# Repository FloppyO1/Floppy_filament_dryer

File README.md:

# Floppy Filament Dryer

This project is a controller board designed for a small electric oven, transforming it into a filament dryer for 3D printing. The controller allows precise temperature management, helping keep your filament dry and ready to use.

## Features

- Temperature control for effective filament drying
- Multiple materials presets
- Timer function
- Two custom material temp available
- Compatible with standard electric ovens
- Easy setup and integration

## YouTube Video

Watch it in action: [Filament Dryer Demo](https://youtu.be/55DRHrMC5Mg)

## License

This project is open source. See the LICENSE file for more details.

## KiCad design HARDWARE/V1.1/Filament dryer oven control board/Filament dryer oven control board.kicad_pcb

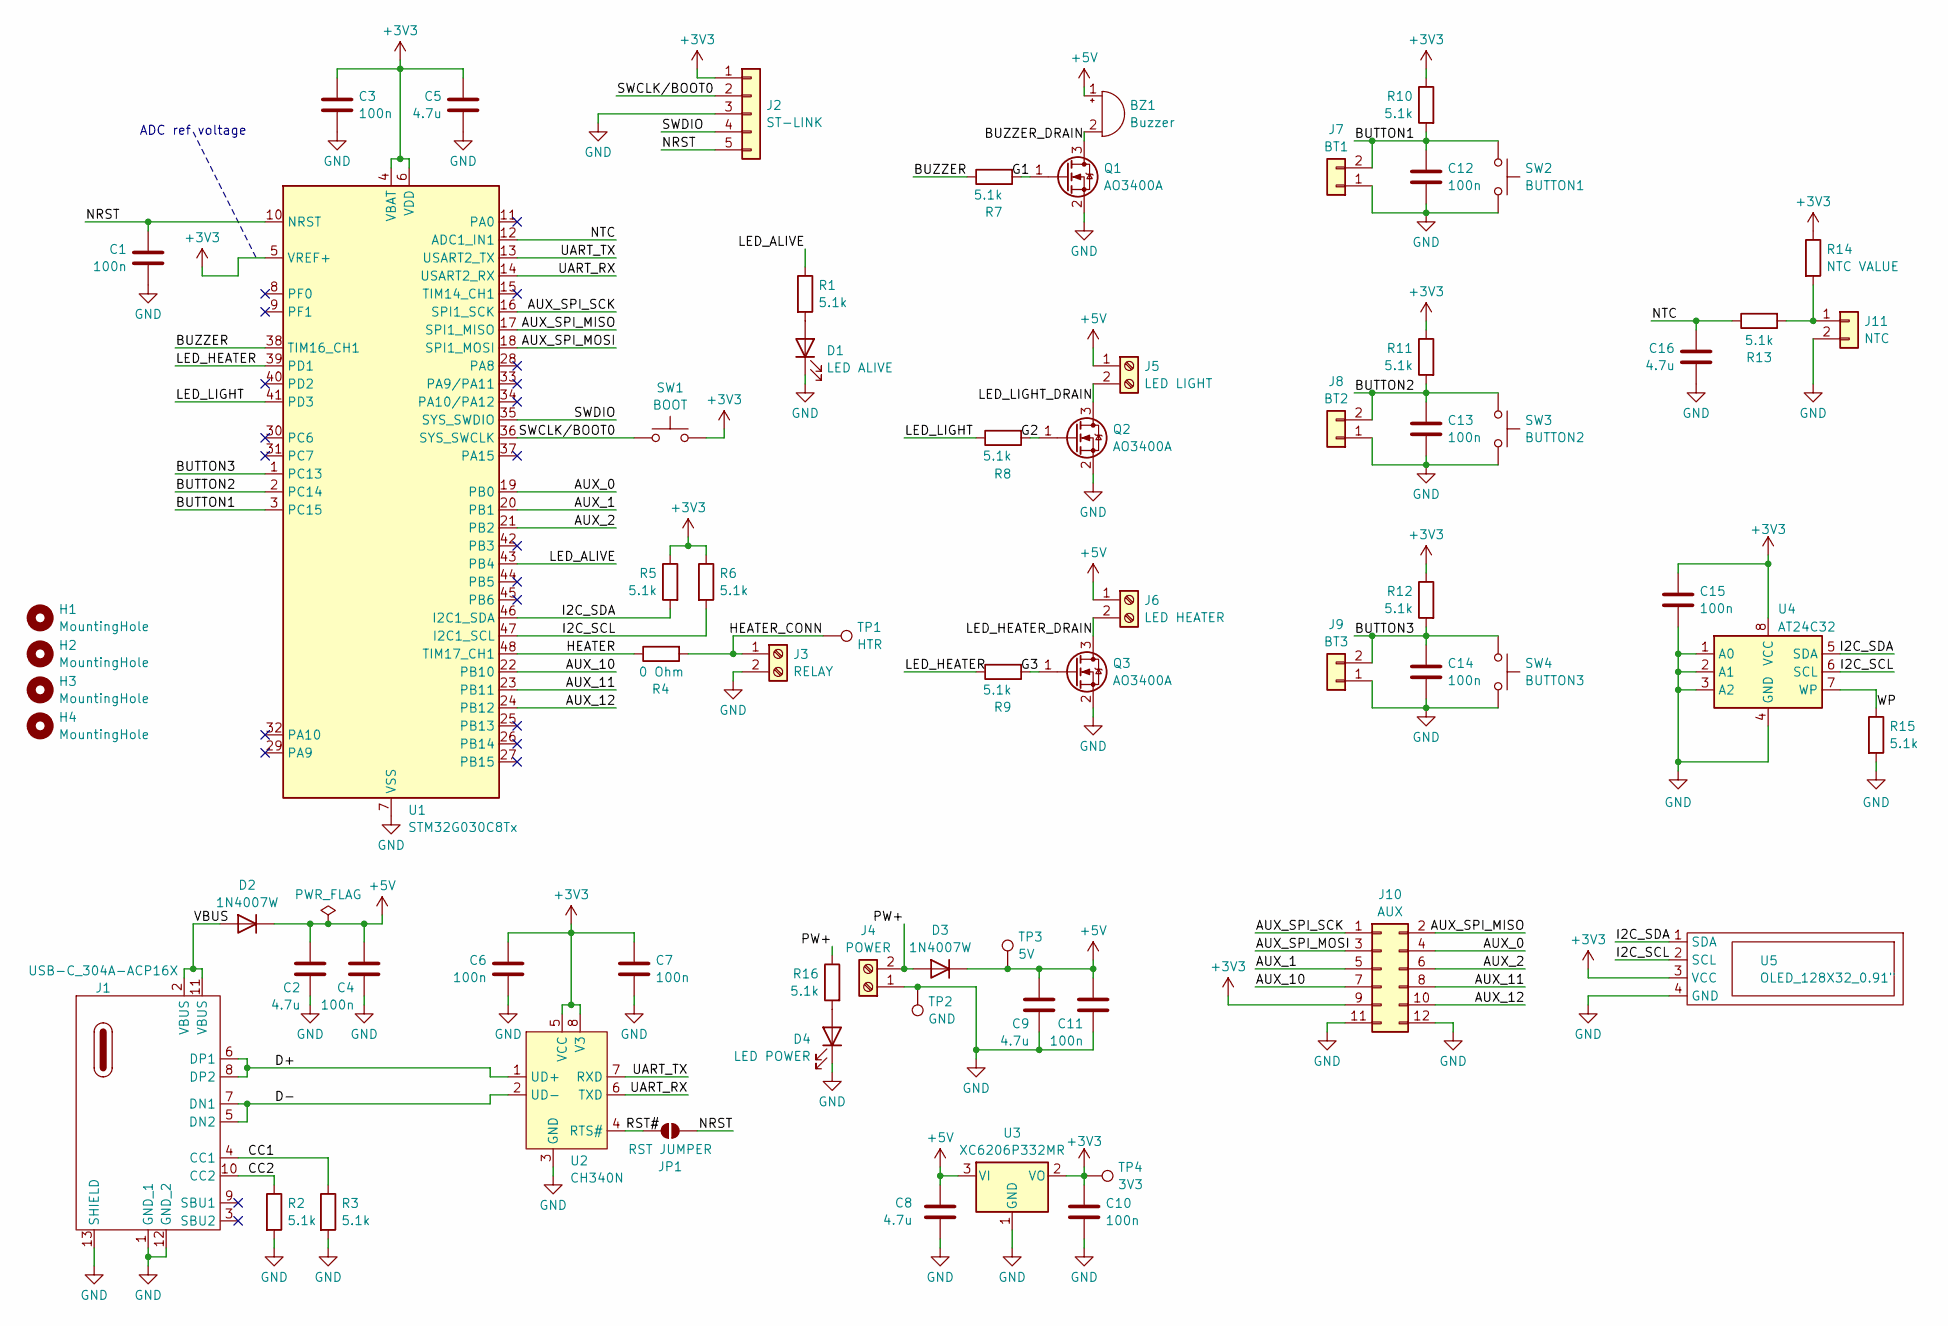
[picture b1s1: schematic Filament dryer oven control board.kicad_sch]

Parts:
BZ1: Buzzer; Buzzer_12x9.5RM7.6
C1, C3, C4, C6, C7, C10, C11, C12, C13, C14, C15: 100n; C_0805_2012Metric_Pad1.18x1.45mm_HandSolder
C2, C5, C8, C9, C16: 4.7u; C_0805_2012Metric_Pad1.18x1.45mm_HandSolder
D1: LED ALIVE; LED_0805_2012Metric_Pad1.15x1.40mm_HandSolder
D2, D3: 1N4007W; D_SOD-123F; LCSC C7528871
D4: LED POWER; LED_0805_2012Metric_Pad1.15x1.40mm_HandSolder
H1, H2, H3, H4: MountingHole; MountingHole_3.2mm_M3_Pad_Via
J1: USB-C_304A-ACP16X; USB_C_304A-ACP16X
J2: ST-LINK; PinHeader_1x05_P2.54mm_Vertical
J3: RELAY; TerminalBlock_bornier-2_P5.08mm
J4: POWER; TerminalBlock_bornier-2_P5.08mm
J5: LED LIGHT; TerminalBlock_bornier-2_P5.08mm
J6: LED HEATER; TerminalBlock_bornier-2_P5.08mm
J7: BT1; JST_XH_B2B-XH-A_1x02_P2.50mm_Vertical
J8: BT2; JST_XH_B2B-XH-A_1x02_P2.50mm_Vertical
J9: BT3; JST_XH_B2B-XH-A_1x02_P2.50mm_Vertical
J10: AUX; PinHeader_2x06_P2.54mm_Vertical
J11: NTC; JST_XH_B2B-XH-A_1x02_P2.50mm_Vertical
JP1: RST JUMPER; SolderJumper-2_P1.3mm_Open_RoundedPad1.0x1.5mm
Q1, Q2, Q3: AO3400A; SOT-23
R1, R2, R3, R5, R6, R7, R8, R9, R10, R11, R12, R13, R15, R16: 5.1k; R_0805_2012Metric_Pad1.20x1.40mm_HandSolder
R4: 0 Ohm; R_0805_2012Metric_Pad1.20x1.40mm_HandSolder
R14: NTC VALUE; R_0805_2012Metric_Pad1.20x1.40mm_HandSolder
SW1: BOOT; SW-SMD_TS24CA SMD BUTTO 90deg
SW2: BUTTON1; SW_SPST_SKQG_WithoutStem
SW3: BUTTON2; SW_SPST_SKQG_WithoutStem
SW4: BUTTON3; SW_SPST_SKQG_WithoutStem
TP1: HTR; TestPoint_THTPad_1.0x1.0mm_Drill0.5mm
TP2: GND; TestPoint_THTPad_1.0x1.0mm_Drill0.5mm
TP3: 5V; TestPoint_THTPad_1.0x1.0mm_Drill0.5mm
TP4: 3V3; TestPoint_THTPad_1.0x1.0mm_Drill0.5mm
U1: STM32G030C8Tx; LQFP-48_7x7mm_P0.5mm
U2: CH340N; SOP-8_3.9x4.9mm_P1.27mm
U3: XC6206P332MR; SOT-23-3
U4: AT24C32; SO-8_3.9x4.9mm_P1.27mm
U5: OLED_128X32_0.91"; PinSocket_1x04_P2.54mm_Vertical

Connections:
+3V3: C3.1, C5.1, C6.1, C7.1, C10.1, C15.1, J2.1, J10.9, R5.1, R6.1, R10.1, R11.1, R12.1, R14.1, SW1.2, TP4.1, U1.4 (VBAT), U1.5 (VREF+), U1.6 (VDD), U2.5 (VCC), U2.8 (V3), U3.2 (VO), U4.8 (VCC), U5.3 (VCC)
+5V: BZ1.1 (+), C2.1, C4.1, C8.1, C9.1, C11.1, D2.1 (K), D3.1 (K), J5.1, J6.1, TP3.1, U3.3 (VI)
/AUX_0: J10.4, U1.19 (PB0)
/AUX_1: J10.5, U1.20 (PB1)
/AUX_2: J10.6, U1.21 (PB2)
/AUX_10: J10.7, U1.22 (PB10)
/AUX_11: J10.8, U1.23 (PB11)
/AUX_12: J10.10, U1.24 (PB12)
/AUX_SPI_MISO: J10.2, U1.17 (SPI1_MISO)
/AUX_SPI_MOSI: J10.3, U1.18 (SPI1_MOSI)
/AUX_SPI_SCK: J10.1, U1.16 (SPI1_SCK)
/BUTTON1: C12.1, J7.2, R10.2, SW2.1, U1.3 (PC15)
/BUTTON2: C13.1, J8.2, R11.2, SW3.1, U1.2 (PC14)
/BUTTON3: C14.1, J9.2, R12.2, SW4.1, U1.1 (PC13)
/BUZZER: R7.1, U1.38 (TIM16_CH1)
/BUZZER_DRAIN: BZ1.2 (-), Q1.3 (D)
/CC1: J1.4 (CC1), R3.1
/CC2: J1.10 (CC2), R2.1
/D+: J1.6 (DP1), J1.8 (DP2), U2.1 (UD+)
/D-: J1.5 (DN2), J1.7 (DN1), U2.2 (UD-)
/G1: Q1.1 (G), R7.2
/G2: Q2.1 (G), R8.2
/G3: Q3.1 (G), R9.2
/HEATER: R4.1, U1.48 (TIM17_CH1)
/HEATER_CONN: J3.1, R4.2, TP1.1
/I2C_SCL: R6.2, U1.47 (I2C1_SCL), U4.6 (SCL), U5.2 (SCL)
/I2C_SDA: R5.2, U1.46 (I2C1_SDA), U4.5 (SDA), U5.1 (SDA)
/LED_ALIVE: R1.1, U1.43 (PB4)
/LED_HEATER: R9.1, U1.39 (PD1)
/LED_HEATER_DRAIN: J6.2, Q3.3 (D)
/LED_LIGHT: R8.1, U1.41 (PD3)
/LED_LIGHT_DRAIN: J5.2, Q2.3 (D)
/NRST: C1.1, J2.5, JP1.1 (A), U1.10 (NRST)
/NTC: C16.1, R13.1, U1.12 (ADC1_IN1)
/PW+: D3.2 (A), J4.2, R16.1
/RST#: JP1.2 (B), U2.4 (RTS#)
/SWCLK/BOOT0: J2.2, SW1.1, U1.36 (SYS_SWCLK)
/SWDIO: J2.4, U1.35 (SYS_SWDIO)
/UART_RX: U1.14 (USART2_RX), U2.6 (TXD)
/UART_TX: U1.13 (USART2_TX), U2.7 (RXD)
/VBUS: D2.2 (A), J1.2 (VBUS), J1.11 (VBUS)
/WP: R15.1, U4.7 (WP)
GND: C1.2, C2.2, C3.2, C4.2, C5.2, C6.2, C7.2, C8.2, C9.2, C10.2, C11.2, C12.2, C13.2, C14.2, C15.2, C16.2, D1.1 (K), D4.1 (K), J1.1 (GND_1), J1.12 (GND_2), J1.13 (SHIELD), J2.3, J3.2, J4.1, J7.1, J8.1, J9.1, J10.11, J10.12, J11.2, Q1.2 (S), Q2.2 (S), Q3.2 (S), R2.2, R3.2, R15.2, SW2.2, SW3.2, SW4.2, TP2.1, U1.7 (VSS), U2.3 (GND), U3.1 (GND), U4.1 (A0), U4.2 (A1), U4.3 (A2), U4.4 (GND), U5.4 (GND)
unnamed: D1.2 (A), R1.2
unnamed: D4.2 (A), R16.2
unnamed: J11.1, R13.2, R14.2

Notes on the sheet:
ADC ref voltage

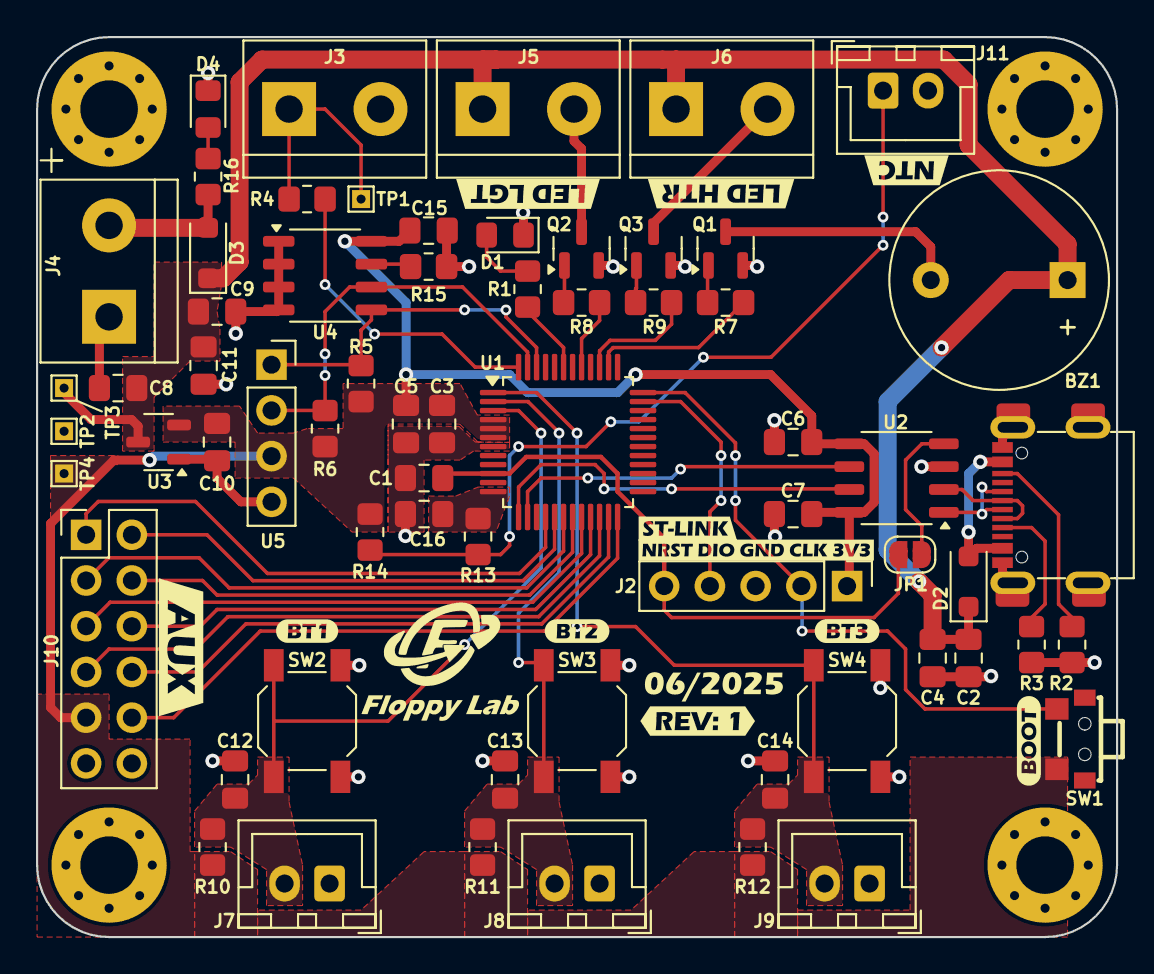
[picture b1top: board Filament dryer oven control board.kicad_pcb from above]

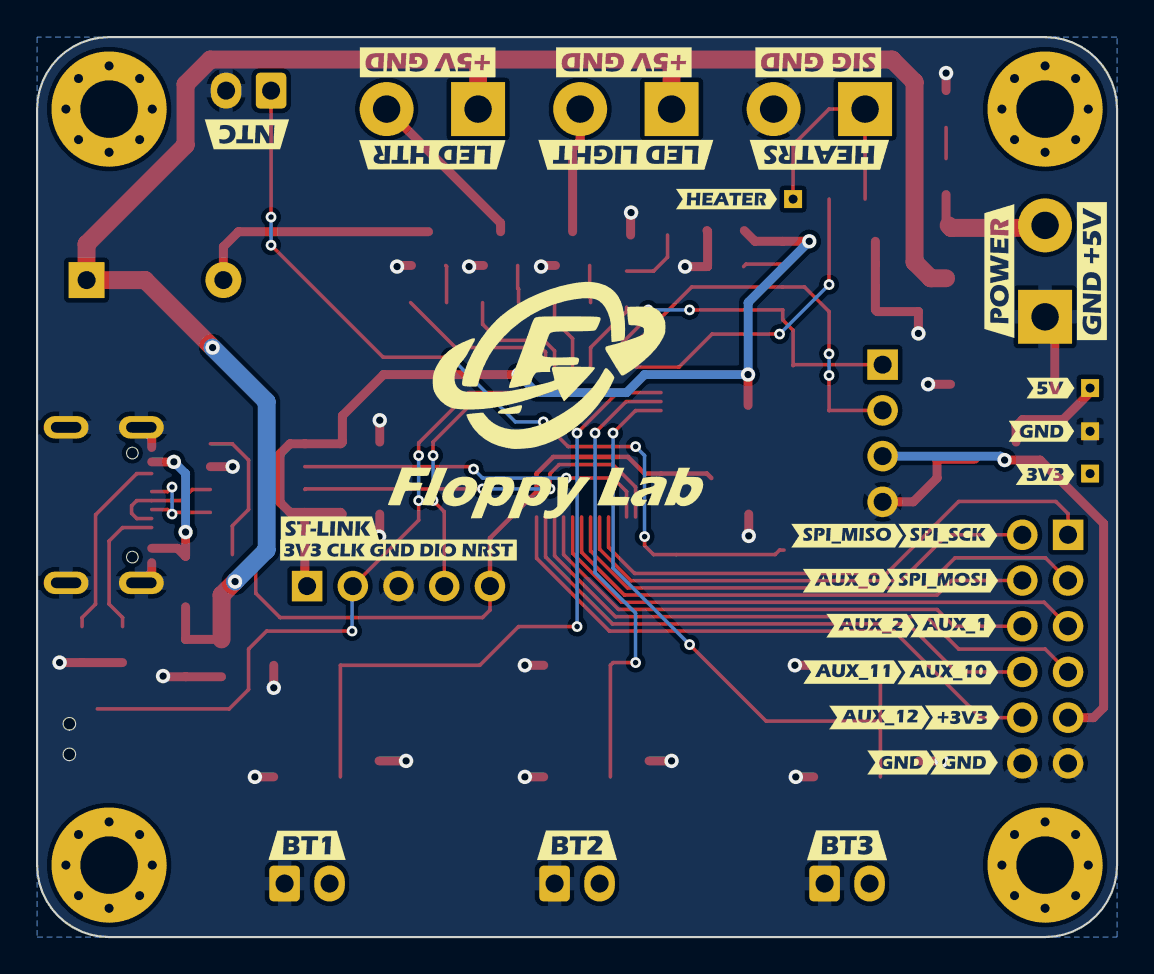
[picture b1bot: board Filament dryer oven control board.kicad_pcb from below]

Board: 2 copper layers, 60.0 x 50.0 mm, 111 parts (30 on the bottom side), 46 nets.

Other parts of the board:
kibuzzard-6853DD8E: G***; kibuzzard-6853DD8E
kibuzzard-6853DD65: G***; kibuzzard-6853DD65
kibuzzard-6853DD93: G***; kibuzzard-6853DD93
kibuzzard-6853DDBD, kibuzzard-6853DDBD#2: G***; kibuzzard-6853DDBD
kibuzzard-6853DE43: G***; kibuzzard-6853DE43
kibuzzard-6853DE79: G***; kibuzzard-6853DE79
kibuzzard-6853DEDF: G***; kibuzzard-6853DEDF
kibuzzard-6853DFAB, kibuzzard-6853DFAB#2: G***; kibuzzard-6853DFAB
kibuzzard-6853DFD3: G***; kibuzzard-6853DFD3
kibuzzard-6853E9B3, kibuzzard-6853E9B3#2: G***; kibuzzard-6853E9B3
kibuzzard-6853E9C2: G***; kibuzzard-6853E9C2
kibuzzard-6853E9F3: G***; kibuzzard-6853E9F3
kibuzzard-6853E92D: G***; kibuzzard-6853E92D
kibuzzard-6853E947: G***; kibuzzard-6853E947
kibuzzard-6853E998: G***; kibuzzard-6853E998
kibuzzard-6853EA0A: G***; kibuzzard-6853EA0A
kibuzzard-6853EB5D: G***; kibuzzard-6853EB5D
kibuzzard-6853EB86: G***; kibuzzard-6853EB86
kibuzzard-6853EBAF: G***; kibuzzard-6853EBAF
kibuzzard-6853EBB8: G***; kibuzzard-6853EBB8
kibuzzard-6853EBDD: G***; kibuzzard-6853EBDD
kibuzzard-6853EBE6: G***; kibuzzard-6853EBE6
kibuzzard-6853EBF5: G***; kibuzzard-6853EBF5
kibuzzard-6853EC00: G***; kibuzzard-6853EC00
kibuzzard-6853EC1A: G***; kibuzzard-6853EC1A
kibuzzard-6853EC51: G***; kibuzzard-6853EC51
kibuzzard-6853EC60, kibuzzard-6853EC60#2: G***; kibuzzard-6853EC60
kibuzzard-6853ECA3: G***; kibuzzard-6853ECA3
kibuzzard-6853ECB2: G***; kibuzzard-6853ECB2
kibuzzard-6853ECDA: G***; kibuzzard-6853ECDA
kibuzzard-6853EE5A: G***; kibuzzard-6853EE5A
kibuzzard-6853EFA6: G***; kibuzzard-6853EFA6
kibuzzard-6853EFB4: G***; kibuzzard-6853EFB4
kibuzzard-6853EFC3: G***; kibuzzard-6853EFC3
kibuzzard-6853EFD6: G***; kibuzzard-6853EFD6
kibuzzard-6853F23E: G***; kibuzzard-6853F23E
kibuzzard-6889D489: G***; kibuzzard-6889D489
kibuzzard-6889D529: G***; kibuzzard-6889D529

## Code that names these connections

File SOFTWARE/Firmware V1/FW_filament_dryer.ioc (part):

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Mcu.Name=STM32G030C(6-8)Tx
Mcu.Package=LQFP48
Mcu.UserName=STM32G030C8Tx
PA1.GPIOParameters=GPIO_Label
PA1.GPIO_Label=NTC_ADC1_IN1
PA1.Mode=IN1
PA1.Signal=ADC1_IN1
PA13.Mode=Serial_Wire
PA13.Signal=SYS_SWDIO
PA14-BOOT0.Mode=Serial_Wire
PA14-BOOT0.Signal=SYS_SWCLK
PA2.Mode=Asynchronous
PA2.Signal=USART2_TX
PA3.Mode=Asynchronous
PA3.Signal=USART2_RX
PB4.GPIOParameters=GPIO_Label
PB4.GPIO_Label=LED_ALIVE
PB4.Signal=GPIO_Output
PB7.Mode=I2C
PB7.Signal=I2C1_SDA
PB8.Mode=I2C
PB8.Signal=I2C1_SCL
PB9.GPIOParameters=GPIO_Label
PB9.GPIO_Label=HEATER_PWM
PB9.Signal=S_TIM17_CH1
PC13.GPIOParameters=GPIO_Label,GPIO_ModeDefaultEXTI
PC13.GPIO_Label=BUTTON3
PC13.GPIO_ModeDefaultEXTI=GPIO_MODE_IT_RISING_FALLING
PC13.Signal=GPXTI13
PC14-OSC32_IN\ (PC14).GPIOParameters=GPIO_Label,GPIO_ModeDefaultEXTI
PC14-OSC32_IN\ (PC14).GPIO_Label=BUTTON2
PC14-OSC32_IN\ (PC14).GPIO_ModeDefaultEXTI=GPIO_MODE_IT_RISING_FALLING
PC14-OSC32_IN\ (PC14).Signal=GPXTI14
PC15-OSC32_OUT\ (PC15).GPIOParameters=GPIO_Label,GPIO_ModeDefaultEXTI
PC15-OSC32_OUT\ (PC15).GPIO_Label=BUTTON1
PC15-OSC32_OUT\ (PC15).GPIO_ModeDefaultEXTI=GPIO_MODE_IT_RISING_FALLING
PC15-OSC32_OUT\ (PC15).Signal=GPXTI15
PD0.GPIOParameters=GPIO_Label
PD0.GPIO_Label=BUZZER_PWM
PD0.Signal=S_TIM16_CH1
PD1.GPIOParameters=GPIO_Label
PD1.GPIO_Label=LED_HEATING
PD1.Signal=GPIO_Output
PD3.GPIOParameters=GPIO_Label
PD3.GPIO_Label=LED_LIGHT
PD3.Signal=GPIO_Output
RCC.HSE_VALUE=8000000
RCC.SYSCLKFreq_VALUE=64000000
RCC.SYSCLKSource=RCC_SYSCLKSOURCE_PLLCLK
board=custom

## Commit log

2025-07-27 Create LICENSE
2025-07-27 UPDATED LICENSE
2025-07-27 images
2025-07-30 fixed some silkscreen
2025-07-30 provided in a good position the .elf file for firmware upload
